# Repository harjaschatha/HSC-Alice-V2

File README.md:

# HSC Alice V2
 Second version of my keyboard

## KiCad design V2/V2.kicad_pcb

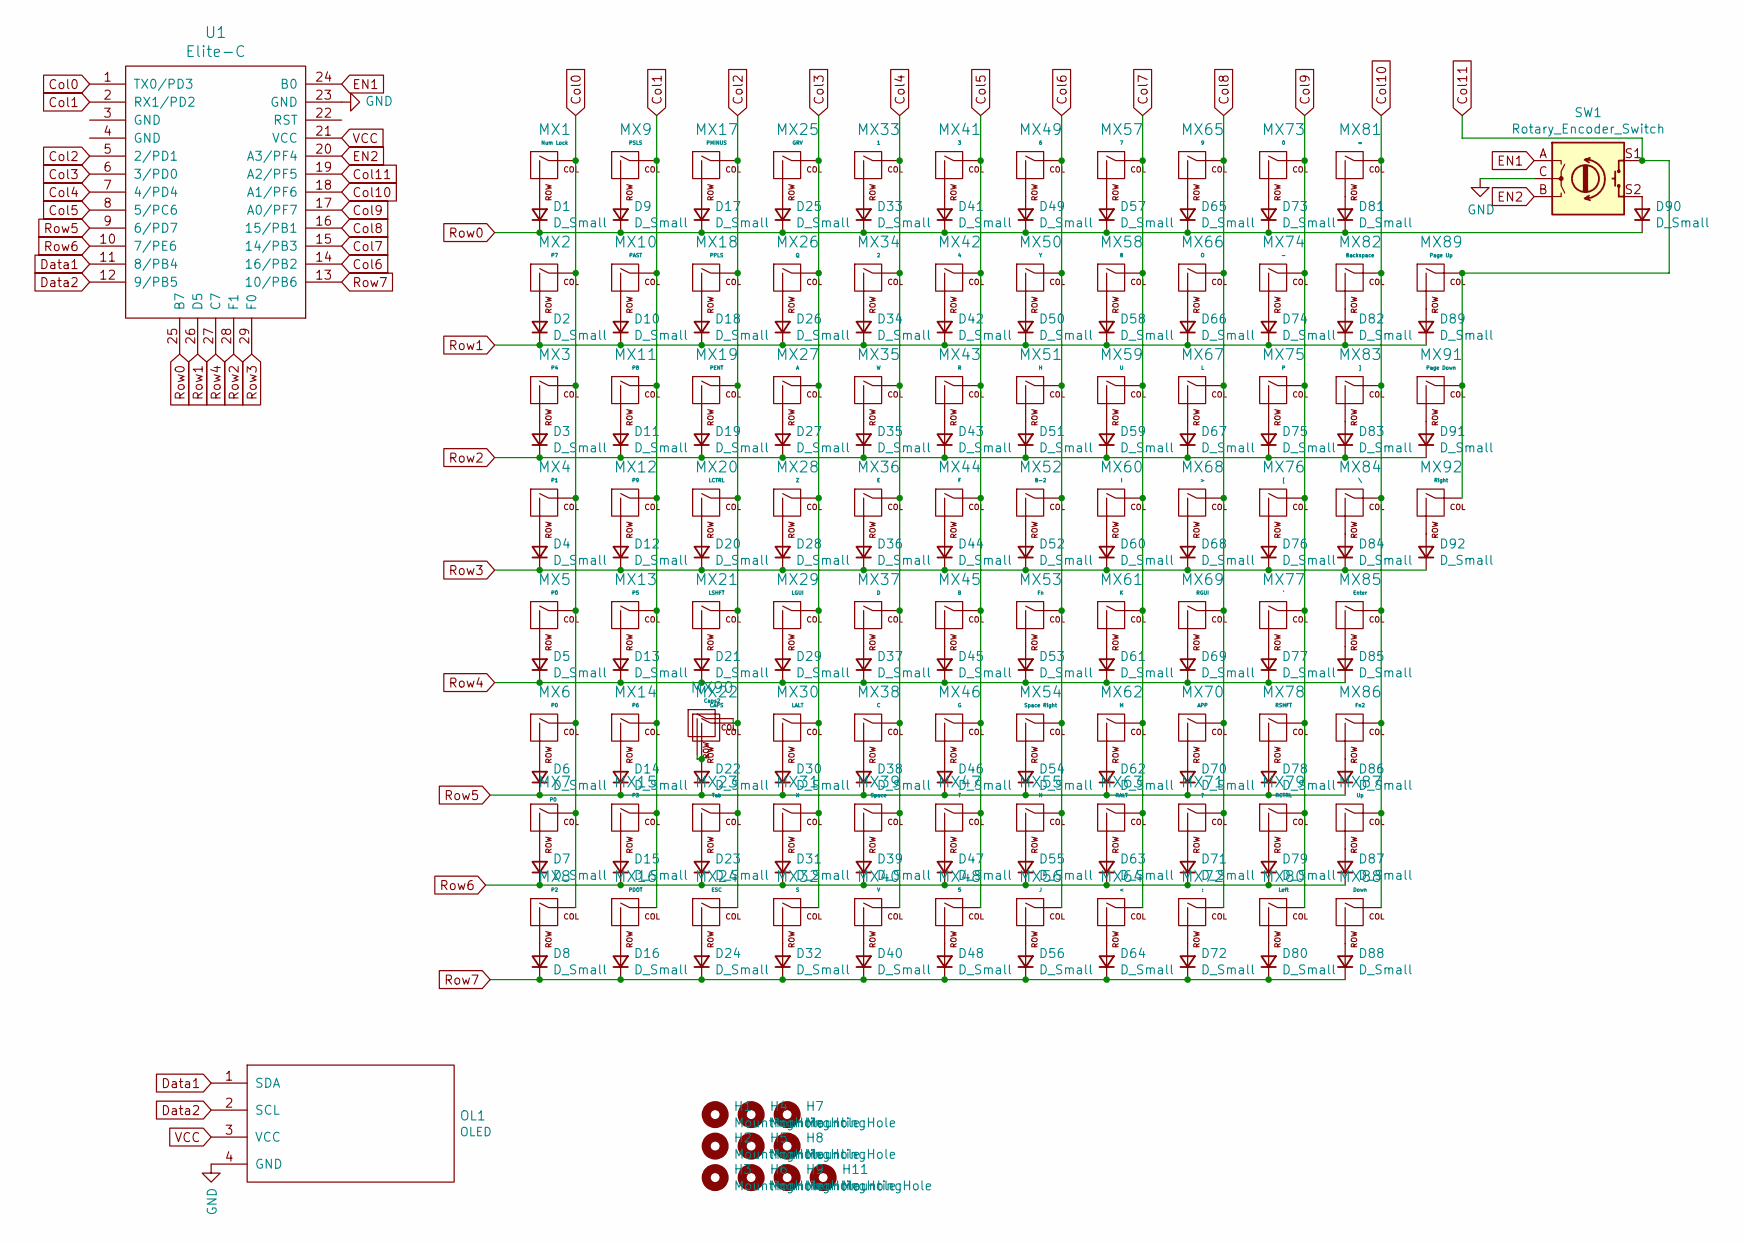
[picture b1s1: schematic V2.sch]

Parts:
D1, D2, D3, D4, D5, D6, D7, D8, D9, D10, D11, D12, D13, D14, D15, D16, D17, D18, D19, D20, D21, D22, D23, D24, D25, D26, D27, D28, D29, D30, D31, D32, D33, D34, D35, D36, D37, D38, D39, D40, D41, D42, D43, D44, D45, D46, D47, D48, D49, D50, D51, D52, D53, D54, D55, D56, D57, D58, D59, D60, D61, D62, D63, D64, D65, D66, D67, D68, D69, D70, D71, D72, D73, D74, D75, D76, D77, D78, D79, D80, D81, D82, D83, D84, D85, D86, D87, D88, D89, D90, D91, D92: D_Small; D_SOD-123
H1, H2, H3, H4, H5, H6, H7, H8, H9, H11: MountingHole; MountingHole_2.2mm_M2_Pad
MX1: Num Lock; MXOnly-1U-NoLED
MX2: P7; MXOnly-1U-NoLED
MX3: P4; MXOnly-1U-NoLED
MX4: P1; MXOnly-1U-NoLED
MX5: P0; MXOnly-2U-ReversedStabilizers-NoLED
MX6, MX7: P0; MXOnly-1U-NoLED
MX8: P2; MXOnly-1U-NoLED
MX9: PSLS; MXOnly-1U-NoLED
MX10: PAST; MXOnly-1U-NoLED
MX11: P8; MXOnly-1U-NoLED
MX12: P9; MXOnly-1U-NoLED
MX13: P5; MXOnly-1U-NoLED
MX14: P6; MXOnly-1U-NoLED
MX15: P3; MXOnly-1U-NoLED
MX16: PDOT; MXOnly-1U-NoLED
MX17: PMINUS; MXOnly-1U-NoLED
MX18: PPLS; MXOnly-2U-NoLED
MX19: PENT; MXOnly-2U-NoLED
MX20: LCTRL; MXOnly-1.25U-NoLED
MX21: LSHFT; MXOnly-2U-NoLED
MX22: CAPS; MXOnly-1.75U-NoLED
MX23: Tab; MXOnly-1.25U-NoLED
MX24: ESC; MXOnly-1U-NoLED
MX25: GRV; MXOnly-1U-NoLED
MX26: Q; MXOnly-1U-NoLED
MX27: A; MXOnly-1U-NoLED
MX28: Z; MXOnly-1U-NoLED
MX29: LGUI; MXOnly-1.25U-NoLED
MX30: LALT; MXOnly-1.25U-NoLED
MX31: X; MXOnly-1U-NoLED
MX32: S; MXOnly-1U-NoLED
MX33: 1; MXOnly-1U-NoLED
MX34: 2; MXOnly-1U-NoLED
MX35: W; MXOnly-1U-NoLED
MX36: E; MXOnly-1U-NoLED
MX37: D; MXOnly-1U-NoLED
MX38: C; MXOnly-1U-NoLED
MX39: Space; MXOnly-2.25U-ReversedStabilizers-NoLED
MX40: V; MXOnly-1U-NoLED
MX41: 3; MXOnly-1U-NoLED
MX42: 4; MXOnly-1U-NoLED
MX43: R; MXOnly-1U-NoLED
MX44: F; MXOnly-1U-NoLED
MX45: B; MXOnly-1U-NoLED
MX46: G; MXOnly-1U-NoLED
MX47: T; MXOnly-1U-NoLED
MX48: 5; MXOnly-1U-NoLED
MX49: 6; MXOnly-1U-NoLED
MX50: Y; MXOnly-1U-NoLED
MX51: H; MXOnly-1U-NoLED
MX52: B-2; MXOnly-1U-NoLED
MX53: Fn; MXOnly-1U-NoLED
MX54: Space Right; MXOnly-2.75U-ReversedStabilizers-NoLED
MX55: N; MXOnly-1U-NoLED
MX56: J; MXOnly-1U-NoLED
MX57: 7; MXOnly-1U-NoLED
MX58: 8; MXOnly-1U-NoLED
MX59: U; MXOnly-1U-NoLED
MX60: I; MXOnly-1U-NoLED
MX61: K; MXOnly-1U-NoLED
MX62: M; MXOnly-1U-NoLED
MX63: RALT; MXOnly-1.25U-NoLED
MX64: <; MXOnly-1U-NoLED
MX65: 9; MXOnly-1U-NoLED
MX66: O; MXOnly-1U-NoLED
MX67: L; MXOnly-1U-NoLED
MX68: >; MXOnly-1U-NoLED
MX69: RGUI; MXOnly-1.25U-NoLED
MX70: APP; MXOnly-1.25U-NoLED
MX71: ?; MXOnly-1U-NoLED
MX72: :; MXOnly-1U-NoLED
MX73: 0; MXOnly-1U-NoLED
MX74: -; MXOnly-1U-NoLED
MX75: P; MXOnly-1U-NoLED
MX76: [; MXOnly-1U-NoLED
MX77: '; MXOnly-1U-NoLED
MX78: RSHFT; MXOnly-2.25U-NoLED
MX79: RCTRL; MXOnly-1.25U-NoLED
MX80: Left; MXOnly-1U-NoLED
MX81: =; MXOnly-1U-NoLED
MX82: Backspace; MXOnly-2U-NoLED
MX83: ]; MXOnly-1U-NoLED
MX84: \\; MXOnly-1.25U-NoLED
MX85: Enter; MXOnly-2U-NoLED
MX86: Fn2; MXOnly-1U-NoLED
MX87: Up; MXOnly-1U-NoLED
MX88: Down; MXOnly-1U-NoLED
MX89: Page Up; MXOnly-1U-NoLED
MX90: Caps2; MXOnly-1.25U-NoLED
MX91: Page Down; MXOnly-1U-NoLED
MX92: Right; MXOnly-1U-NoLED
OL1: OLED; OLED_v2
SW1: Rotary_Encoder_Switch; RotaryEncoder_Alps_EC11E-Switch_Vertical_H20mm
U1: Elite-C; Elite-C-castellated-29pin-holes

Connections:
Col0: MX1.1 (COL), MX2.1 (COL), MX3.1 (COL), MX4.1 (COL), MX5.1 (COL), MX6.1 (COL), MX7.1 (COL), MX8.1 (COL), U1.1 (TX0/PD3)
Col1: MX9.1 (COL), MX10.1 (COL), MX11.1 (COL), MX12.1 (COL), MX13.1 (COL), MX14.1 (COL), MX15.1 (COL), MX16.1 (COL), U1.2 (RX1/PD2)
Col2: MX17.1 (COL), MX18.1 (COL), MX19.1 (COL), MX20.1 (COL), MX21.1 (COL), MX22.1 (COL), MX23.1 (COL), MX24.1 (COL), MX90.1 (COL), U1.5 (2/PD1)
Col3: MX25.1 (COL), MX26.1 (COL), MX27.1 (COL), MX28.1 (COL), MX29.1 (COL), MX30.1 (COL), MX31.1 (COL), MX32.1 (COL), U1.6 (3/PD0)
Col4: MX33.1 (COL), MX34.1 (COL), MX35.1 (COL), MX36.1 (COL), MX37.1 (COL), MX38.1 (COL), MX39.1 (COL), MX40.1 (COL), U1.7 (4/PD4)
Col5: MX41.1 (COL), MX42.1 (COL), MX43.1 (COL), MX44.1 (COL), MX45.1 (COL), MX46.1 (COL), MX47.1 (COL), MX48.1 (COL), U1.8 (5/PC6)
Col6: MX49.1 (COL), MX50.1 (COL), MX51.1 (COL), MX52.1 (COL), MX53.1 (COL), MX54.1 (COL), MX55.1 (COL), MX56.1 (COL), U1.14 (16/PB2)
Col7: MX57.1 (COL), MX58.1 (COL), MX59.1 (COL), MX60.1 (COL), MX61.1 (COL), MX62.1 (COL), MX63.1 (COL), MX64.1 (COL), U1.15 (14/PB3)
Col8: MX65.1 (COL), MX66.1 (COL), MX67.1 (COL), MX68.1 (COL), MX69.1 (COL), MX70.1 (COL), MX71.1 (COL), MX72.1 (COL), U1.16 (15/PB1)
Col9: MX73.1 (COL), MX74.1 (COL), MX75.1 (COL), MX76.1 (COL), MX77.1 (COL), MX78.1 (COL), MX79.1 (COL), MX80.1 (COL), U1.17 (A0/PF7); also elsewhere on the board
Col10: MX81.1 (COL), MX82.1 (COL), MX83.1 (COL), MX84.1 (COL), MX85.1 (COL), MX86.1 (COL), MX87.1 (COL), MX88.1 (COL), U1.18 (A1/PF6)
Col11: MX89.1 (COL), MX91.1 (COL), MX92.1 (COL), SW1.S1, U1.19 (A2/PF5)
Data1: OL1.1 (SDA), U1.11 (8/PB4)
Data2: OL1.2 (SCL), U1.12 (9/PB5)
EN1: SW1.A, U1.24 (B0)
EN2: SW1.B, U1.20 (A3/PF4)
GND: OL1.4 (GND), SW1.C, U1.23 (GND)
unnamed: D1.2 (A), MX1.2 (ROW)
unnamed: D2.2 (A), MX2.2 (ROW)
unnamed: D3.2 (A), MX3.2 (ROW)
unnamed: D4.2 (A), MX4.2 (ROW)
unnamed: D5.2 (A), MX5.2 (ROW)
unnamed: D6.2 (A), MX6.2 (ROW)
unnamed: D7.2 (A), MX7.2 (ROW)
unnamed: D8.2 (A), MX8.2 (ROW)
unnamed: D9.2 (A), MX9.2 (ROW)
unnamed: D10.2 (A), MX10.2 (ROW)
unnamed: D11.2 (A), MX11.2 (ROW)
unnamed: D12.2 (A), MX12.2 (ROW)
unnamed: D13.2 (A), MX13.2 (ROW)
unnamed: D14.2 (A), MX14.2 (ROW)
unnamed: D15.2 (A), MX15.2 (ROW)
unnamed: D16.2 (A), MX16.2 (ROW)
unnamed: D17.2 (A), MX17.2 (ROW)
unnamed: D18.2 (A), MX18.2 (ROW)
unnamed: D19.2 (A), MX19.2 (ROW)
unnamed: D20.2 (A), MX20.2 (ROW)
unnamed: D21.2 (A), MX21.2 (ROW)
unnamed: D22.2 (A), MX22.2 (ROW), MX90.2 (ROW)
unnamed: D23.2 (A), MX23.2 (ROW)
unnamed: D24.2 (A), MX24.2 (ROW)
unnamed: D25.2 (A), MX25.2 (ROW)
unnamed: D26.2 (A), MX26.2 (ROW)
unnamed: D27.2 (A), MX27.2 (ROW)
unnamed: D28.2 (A), MX28.2 (ROW)
unnamed: D29.2 (A), MX29.2 (ROW)
unnamed: D30.2 (A), MX30.2 (ROW)
unnamed: D31.2 (A), MX31.2 (ROW)
unnamed: D32.2 (A), MX32.2 (ROW)
unnamed: D33.2 (A), MX33.2 (ROW)
unnamed: D34.2 (A), MX34.2 (ROW)
unnamed: D35.2 (A), MX35.2 (ROW)
unnamed: D36.2 (A), MX36.2 (ROW)
unnamed: D37.2 (A), MX37.2 (ROW)
unnamed: D38.2 (A), MX38.2 (ROW)
unnamed: D39.2 (A), MX39.2 (ROW)
unnamed: D40.2 (A), MX40.2 (ROW)
unnamed: D41.2 (A), MX41.2 (ROW)
unnamed: D42.2 (A), MX42.2 (ROW)
unnamed: D43.2 (A), MX43.2 (ROW)
unnamed: D44.2 (A), MX44.2 (ROW)
unnamed: D45.2 (A), MX45.2 (ROW)
unnamed: D46.2 (A), MX46.2 (ROW)
unnamed: D47.2 (A), MX47.2 (ROW)
unnamed: D48.2 (A), MX48.2 (ROW)
unnamed: D49.2 (A), MX49.2 (ROW)
unnamed: D50.2 (A), MX50.2 (ROW)
unnamed: D51.2 (A), MX51.2 (ROW)
unnamed: D52.2 (A), MX52.2 (ROW)
unnamed: D53.2 (A), MX53.2 (ROW)
unnamed: D54.2 (A), MX54.2 (ROW)
unnamed: D55.2 (A), MX55.2 (ROW)
unnamed: D56.2 (A), MX56.2 (ROW)
unnamed: D57.2 (A), MX57.2 (ROW)
unnamed: D58.2 (A), MX58.2 (ROW)
unnamed: D59.2 (A), MX59.2 (ROW)
unnamed: D60.2 (A), MX60.2 (ROW)
unnamed: D61.2 (A), MX61.2 (ROW)
unnamed: D62.2 (A), MX62.2 (ROW)
unnamed: D63.2 (A), MX63.2 (ROW)
unnamed: D64.2 (A), MX64.2 (ROW)
unnamed: D65.2 (A), MX65.2 (ROW)
unnamed: D66.2 (A), MX66.2 (ROW)
unnamed: D67.2 (A), MX67.2 (ROW)
unnamed: D68.2 (A), MX68.2 (ROW)
unnamed: D69.2 (A), MX69.2 (ROW)
unnamed: D70.2 (A), MX70.2 (ROW)
unnamed: D71.2 (A), MX71.2 (ROW)
unnamed: D72.2 (A), MX72.2 (ROW)
unnamed: D73.2 (A), MX73.2 (ROW)
unnamed: D74.2 (A), MX74.2 (ROW)
unnamed: D75.2 (A), MX75.2 (ROW)
unnamed: D76.2 (A), MX76.2 (ROW)
unnamed: D77.2 (A), MX77.2 (ROW)
unnamed 94: D78.2 (A), MX78.2 (ROW); also elsewhere on the board
unnamed: D79.2 (A), MX79.2 (ROW)
unnamed: D80.2 (A), MX80.2 (ROW)
unnamed: D81.2 (A), MX81.2 (ROW)
unnamed: D82.2 (A), MX82.2 (ROW)
unnamed: D83.2 (A), MX83.2 (ROW)
unnamed: D84.2 (A), MX84.2 (ROW)
unnamed: D85.2 (A), MX85.2 (ROW)
unnamed: D86.2 (A), MX86.2 (ROW)
unnamed: D87.2 (A), MX87.2 (ROW)
unnamed: D88.2 (A), MX88.2 (ROW)
unnamed: D89.2 (A), MX89.2 (ROW)
unnamed: D90.2 (A), SW1.S2
unnamed: D91.2 (A), MX91.2 (ROW)
unnamed: D92.2 (A), MX92.2 (ROW)
Row0: D1.1 (K), D9.1 (K), D17.1 (K), D25.1 (K), D33.1 (K), D41.1 (K), D49.1 (K), D57.1 (K), D65.1 (K), D73.1 (K), D81.1 (K), D90.1 (K), U1.25 (B7)
Row1: D2.1 (K), D10.1 (K), D18.1 (K), D26.1 (K), D34.1 (K), D42.1 (K), D50.1 (K), D58.1 (K), D66.1 (K), D74.1 (K), D82.1 (K), D89.1 (K), U1.26 (D5)
Row2: D3.1 (K), D11.1 (K), D19.1 (K), D27.1 (K), D35.1 (K), D43.1 (K), D51.1 (K), D59.1 (K), D67.1 (K), D75.1 (K), D83.1 (K), D91.1 (K), U1.28 (F1)
Row3: D4.1 (K), D12.1 (K), D20.1 (K), D28.1 (K), D36.1 (K), D44.1 (K), D52.1 (K), D60.1 (K), D68.1 (K), D76.1 (K), D84.1 (K), D92.1 (K), U1.29 (F0)
Row4: D5.1 (K), D13.1 (K), D21.1 (K), D29.1 (K), D37.1 (K), D45.1 (K), D53.1 (K), D61.1 (K), D69.1 (K), D77.1 (K), D85.1 (K), U1.27 (C7)
Row5: D6.1 (K), D14.1 (K), D22.1 (K), D30.1 (K), D38.1 (K), D46.1 (K), D54.1 (K), D62.1 (K), D70.1 (K), D78.1 (K), D86.1 (K), U1.9 (6/PD7)
Row6: D7.1 (K), D15.1 (K), D23.1 (K), D31.1 (K), D39.1 (K), D47.1 (K), D55.1 (K), D63.1 (K), D71.1 (K), D79.1 (K), D87.1 (K), U1.10 (7/PE6)
Row7: D8.1 (K), D16.1 (K), D24.1 (K), D32.1 (K), D40.1 (K), D48.1 (K), D56.1 (K), D64.1 (K), D72.1 (K), D80.1 (K), D88.1 (K), U1.13 (10/PB6)
VCC: OL1.3 (VCC), U1.21 (VCC)

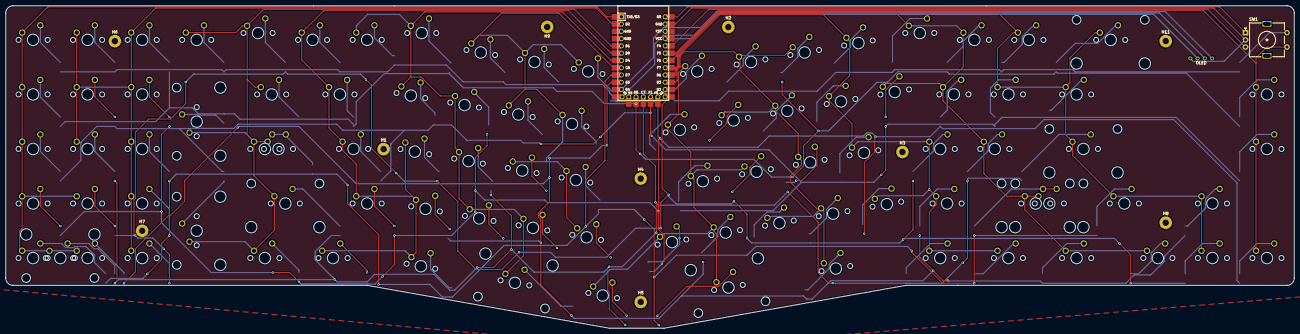
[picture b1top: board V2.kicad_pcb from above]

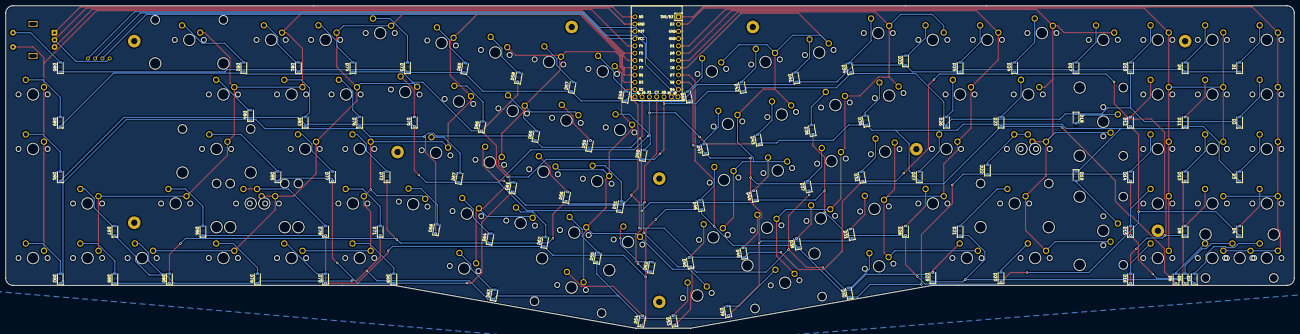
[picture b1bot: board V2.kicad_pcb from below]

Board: 2 copper layers, 450.0 x 112.6 mm, 198 parts (92 on the bottom side), 118 nets.

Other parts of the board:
MX78#2: RSHFT; MXOnly-2.25U-NoLED

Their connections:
Col9: MX78#2.1; also elsewhere on the board
unnamed 94: MX78#2.2; also elsewhere on the board

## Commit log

2021-07-11 Add Library and Schematic
    Added Libraries and Tested Schematic
2021-07-11 Assigned Footprints
2021-07-12 Updated schematic and pcb design
2021-07-24 Added Edge Cuts
2021-07-25 Finished PCB
2021-07-25 Exported Gerber Files
2021-08-06 Switched to LED
2021-08-07 Error Fixed
2021-08-08 Update PCB
2021-08-22 Complete Redesign
2021-08-22 Update PCB and gerber
2021-08-25 Finished Edits
2021-09-06 Final Update
2021-10-17 Fixing Errors
2022-01-23 Update V2.kicad_pcb
    Fixed Enter shift and space size
2022-01-23 Update fp-info-cache
2022-01-24 Edit Gerber Files
